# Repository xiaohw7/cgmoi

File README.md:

# CGMOI User Guide

## Overview

The CGMOI machine is one that is capable of measuring the Centre of Gravity (CG) and Moment Of Inertia (MOI) of a nano-satellite while satellite is mounted on the top plate as shown in picture below.

The concept of this machine is based on [this research paper](https://github.com/xiaohw7/cgmoi/blob/main/applsci-08-00104.pdf) done by researchers from ZheJiang University. It uses 3 load cells in a circle spaced 120 degrees apart to measure CG and a gyroscope to measure acceleration which in turn can be used to obtain MOI.

The machine also includes a stepper motor that spins the top plate, and linear actuators to raise and lower the load cells in order to measure CG.

The stepper motor, linear actuator, gyroscope, load cells and other components are controlled by and wired to an Arduino mega board. The Arduino could then be plugged into a laptop running the Arduino IDE where code could be uploaded to run the CGMOI machine.

Each load cell is marked load cell 1/2/3 on the load cell itself. Linear actuator 1/2/3 correspond to load cell 1/2/3. i.e. linear actuator 1 is directly below load cell 1.

## Components of the CGMOI Machine

- HX711 analog to digital converter

- Single pole double throw(SPDT) relay

- Double pole double throw(DPDT) relay

- Gyroscope

- Power supply (12v and 36v)

- Printed circuit Board

## How to use

1. User would have to download the following Arduino libraries:
      - [HX711_ADC](https://github.com/olkal/HX711_ADC) for the load cells
      - [hanyazou](https://github.com/hanyazou/BMI160-Arduino) for the BMI160 gyroscope
      - [AccelStepper](https://github.com/waspinator/AccelStepper) for stepper motor and stepper motor driver
      - [FreeRTOS](https://github.com/feilipu/Arduino_FreeRTOS_Library) for running Real Time Operating System on Arduino
      - [SimpleKalmanFilter](https://github.com/denyssene/SimpleKalmanFilter) for running values through a Kalman filter to reduce noisy readings

2. Upload cgmoi2.ino onto Arduino and open Serial monitor. Serial monitor to use 9600 baud. Stepper motor driver should be set to 1600 pulse/rev.

3. Code uses FreeRTOS. There will be 4 tasks, namely Rotate, Gyro, Motor, and Cg. Code will suspend Rotate, Gyro, and Motor task immediately in void setup() and Cg task will run at highest priority.

4. Code has 3 modes. Mode CG runs Cg task, reads values from load cells and output CG and mass values. Mode MOI runs Motor and Gyro tasks and outputs angular acceleration values. Mode ROTATE runs Rotate task and allows user to rotate top plate a desired number of steps in either direction.

5. After uploading code, Arduino will be running mode CG and user can see output values from load cells on Serial monitor. User can either continue with mode CG to measure CG of satellite, switch to mode MOI to measure MOI of satellite instead or switch to mode ROTATE to rotate top plate to the desired orientation.

6. Mode CG: User intends to measure CG of satellite

      * Linear actuators must be fully extended.

      * It is advisable to test each linear actuator by moving them up and down individually for 1 second before raising all three actuators completely. Refer to "Commands to send" table below for commands to move actuators individually.

      * Ensure ***screw securing removeable shaft (shown below) is removed*** before sending '9' in Serial monitor to raise linear actuators completely. Then, send '11' in serial monitor to tare load cells before mounting satellite.

      * 

      * Directions of x and y axis are indicated on the top plate and also illustrated in "Calculations" section below.

      * To ease measuring process of CG, x and y axis on top plate must align with axis indicated in "Calculations" section below. Arrow of y axis must point directly away from load cell 1. Location of origin is the center of the top plate.

      * One way to align x and y axis is to align the marked line on the edge of the top plate with the number 1 indicated on load cell 1(marked line should be on the edge of the top plate and positioned 90 degrees counter clockwise from the gyroscope when looking from above the gyroscope mounting point). User can do so with the help of mode 3. An illustration is shown below.

      * 

      * While running task Cg, mass and CG coordinates can be read straight off the output on the Serial monitor. Refer to "Calculations" section below for x and y axis. Coordinates are in mm.

      * User can send '14' to switch to mode MOI and measure MOI of satellite.

      * User can send '16' to switch to mode ROTATE and to rotate top plate.

7. Mode MOI: user intends on measuring MOI of satellite

      * Linear actuators must be fully retracted. Send '10' while in mode CG to fully retract linear actuators.

      * Ensure screw securing removeable shaft (shown above) is secured, send '14' to switch from mode CG to mode MOI.

      * Mode MOI uses 'stepper' instance of AccelStepper class to control stepper motor.

      * Gyro and Motor tasks will run simultaneously and angular acceleration values can be read from serial monitor. Motor will spin back and forth to allow gyro to measure acceleration values. Once measurement process is finished, average acceleration will be displayed on serial monitor along with "Finish recording" message. User has 15 seconds to mount/dismount satellite before recording process starts again.

      * User should record down angular acceleration values with and without satellite mounted. Refer to "Calculations" section for the equations to obtain MOI.

      * While running mode MOI, user can also send '15' to switch to mode CG and return to reading values from load cells.

      * While running mode MOI, user can send '16' to switch to mode ROTATE to rotate top plate.

8. Mode ROTATE: user intends to rotate top plate

      * Linear actuators must be fully retracted. Send '10' while in mode CG to fully retract linear actuators.

      * Ensure screw securing removeable shaft (shown above) is secured, send '16' to switch from mode CG to mode ROTATE.

      * User can input number of steps user wishes stepper motor to turn.

      * Mode ROTATE uses 'rotate' instance of the AccelStepper class. A separate instance from the one used in mode MOI. Hence when user first uploads `cgmoi2.ino`, mode ROTATE regards the position of the stepper motor at that instant as 0 (origin). User can instruct stepper motor to rotate to a specific position that is a certain number of steps away from the origin. Positive steps are in the clockwise direction from origin while negative steps are in the counter clockwise direction from origin.

      * Note that location of origin stays the same the whole time while using the code until Arduino is refreshed. Therefore if user inputs 3000 (motor rotates 3000 steps in clockwise direction from origin) and then inputs 1000, motor would subsequently rotate 2000 steps in the counter clockwise direction and stop at the position that is 1000 steps clockwise from the origin.

      * If user uses mode ROTATE to rotate to 3000 steps clockwise, and then proceeds to use mode MOI, mode MOI will alter the position of the stepper motor but mode ROTATE will still think it is at 3000 steps clockwise. Hence if user then goes back to mode ROTATE and inputs 0, motor will rotate 3000 steps counter clockwise.

      * ***Ensure serial monitor is set to 'No line ending'.***

      * While running mode ROTATE, user can send '15' to switch to mode CG and return to reading values from load cells.

      * While running mode ROTATE, user can send '14' to switch to mode MOI and measure MOI of satellite.

Below is an illustration of how to navigate between the three modes:

***
```
            (User uploads code)
                 |       
                 |   ----------------<--------------------------   
                 |   |                                         |
                 v   v                                         |
            -->(Mode CG)------->---------------                |
            |      |                          |                |
*send '15'* |      | *send '14'*              | *send '16'     ^ *send '15'*
            ^      |                          |                |
            |      v        *send '16'        v                |
            ---(Mode MOI)--------->----(Mode ROTATE)----->------
                   ^                          |
                   |       *send '14'         |
                   -------------<--------------  
```
***

## Commands to send

|Mode |Commands that can be sent |What it does|
|-----|--------------------------|------------|
|CG |Send '1' |Turn on power to linear actuators|
|CG |Send '2' |Turn off power to linear actuators|
|CG |Send '3'/'5'/'7' |Move linear actuator 1/2/3 up for 1 second|
|CG |Send '4'/'6'/'8' |Move linear actuator 1/2/3 down for 1 second|
|CG |Send '9' |Move all 3 linear actuators up fully|
|CG |Send '10' |Move all 3 linear actuators down fully|
|CG |Send '11' |Tare all load cells|
|CG |Send '12' |Turn on power to stepper motor|
|CG |Send '13' |Turn off power to stepper motor|
|CG |Send '14' |End Cg task and resume/start Gyro and Motor tasks, switch to mode MOI|
|CG |Send '16' |End Cg task and resume/start Rotate task, switch to mode ROTATE|
|MOI |Send '12' |Turn on power to stepper motor|
|MOI |Send '13' |Turn off power to stepper motor|
|MOI |Send '15' |End Gyro and Motor tasks and resume/start Cg task, switch to mode CG|
|MOI |Send '16' |End Gyro and Motor tasks and resume/start Rotate task, switch to mode ROTATE|
|ROTATE |Send '12' |Turn on power to stepper motor|
|ROTATE |Send '13' |Turn off power to stepper motor|
|ROTATE |Send '14' |End Rotate task and resume/start Gyro and Motor tasks, switch to mode MOI|
|ROTATE |Send '15' |End Rotate task and resume/start Cg task, switch to mode CG|
|ROTATE |Send steps to rotate |Motor rotate to set steps|

## Points to take note

- Before raising/lowering linear actuators, user must remember to ***remove screw securing removeable shaft***.

- When lowering top plate, user should stand by and make sure removeable shaft enters designated slot correctly.

- Before measuring CG, user to ensure that the tips of adjustable screws (shown below) on load cells are the same distance above the table top so that when top plate is resting on load cells, top plate is as flat as possible.

- Before measuring MOI, ensure screw securing removeable shaft is tightened to prevent any play when motor is turning.

- FreeRTOS can be buggy which causes starting position of gyroscope to shift after repeatedly using mode MOI. Hence it is recommended to position gyro chip above red tape using mode ROTATE before using mode MOI to measure angular acceleration.

- There is a tendency for SPDT relay supplying power to stepper motor to get stuck in the close position despite the LED light being off and signal sent to it to disconnect. This may be because relay is only rated for 30V while power supply is at 36V. Tapping the blue box on the relay would help to disconnect it. User can tell if power had been disconnected by observing light on stepper motor driver.

- Angular acceleration values is rather unreliable and difference while loaded and unloaded may not be easily observed. Sometimes loaded values may even be higher than unloaded values. May be due to looseness and play at the epoxy region of removeable shaft.

- First measurements of angular velocity tend to be buggy and inaccurate, hence code only starts recording values from second reading onwards.

- If load cell readings become inaccurate, try running "Calibration" example from this [github library](https://github.com/olkal/HX711_ADC) and obtain calibration values for each individual load cell and input into the code.

- If there is a need to stop measurements/linear actuators/stepper motor immediately, unplug Arduino to "Emergency Stop".

## Calculations

With reference to image above, points A,B,C correspond to load cell 1,2,3 respectively. Load cell numbers are marked on load cells.

1. Finding Mass

      * Pa = m4 - m1
      * Pc = m6 - m3
      * Pb = m5 - m2
      * Mass of satellite, M = Pa + Pb + Pc  
      * m1, m2 and m3 are weights of fixture tools and platform on load cell A, B and C respectively.
      * m4, m5 and m6 are weights of fixture tools, platform and satellite on load cell A, B and C respectively.
      * Pa, Pb and Pc are satellite weights on load cell a, b and c respectively.
      * Code outputs overall mass of satellite in grams.

2. Finding Centre of Gravity

      * Y-coordinate, yG = [Pb(y2) + Pc(y3) − Pa(y1)]/M
      * X-coordinate, xG = [Pb(x1) − Pc(x2)]/M
      * y1, y2, y3 are distances of points A, B, ad C from y-axis respectively. y1 = 206mm, y2 and y3 = 103mm
      * x1, x2, are distances of point B and C from x-axis. x1 and x2 = 178.4mm
      * Lengths are calculated using values from [load cell plate drawing](https://github.com/xiaohw7/cgmoi/blob/main/M02_load%20cell%20plate_drawing.pdf) and [load cell data sheet](https://github.com/xiaohw7/cgmoi/blob/main/M02_load%20cell%20plate_drawing.pdf).
      * To obtain z-coordinate of CG, rotate satellite by 90 degrees and undergo same calculations to obtain z-coordinate.
      * Code outputs coordinate of CG with reference to axis above and in millimeters.

3. Finding Moment Of Inertia

      * 

      * Use equation above to obtain J1. Where J1 is MOI of satellite. J0 is MOI of fixture tools which can be obtained from solid works. Shown in picture below, J0 in the vertical axis, taken at output coordinate system with center of top plate as origin, is ***19113908.45 grams * square millimeters***.
      * 
      *  Referring again to equation to obtain J1, w0 is angular velocity at time t without satellite. w’0 is angular velocity at time t with satellite. t1 and t2 are time at which angular velocity w0 and w’0 is taken respectively.
      * Thus it is observed that the fraction in the equation is angular acceleration without satellite mounted divided by angular acceleration with satellite mounted.
      * Code outputs angular acceleration values in degrees/sec^2 which can then be used to calculate J0.

      * Rotating about X-axis of satellite will result in JX

      * Rotating about Y-axis of satellite will result in JY

      * Rotating about Z-axis of satellite will result in JZ

      * 

      * Above equation uses parallel axis parallel axis theorem to correct MOI vector with reference to the CG and find vector of MOI. JxG, JyG, JzG are the MOI in x, y, and z direction respectively.

## Areas for improvement

1. Values for angular acceleration can vary substantially leading to inaccurate and imprecise values of MOI.

     * One way to improve is to move designated mounting place of BMI160 chip to the center of the top plate. This way Arduino can use raw values of angular velocity measured by the gyroscope in the MOI equation instead of having to measure linear acceleration values and then subject them to a series of calculations to obtain angular acceleration.

     * Another way is to decrease the play in the removeable shaft especially at the spot with Epoxy where the shaft connects with the flat plate.

2. Torque of stepper motor varies with speed and is difficult to control. This may lead to inaccurate values of MOI when torque applied while top plate is loaded vs when it is unloaded is different.

     *  Potential way to improve is to change to motor to a simple DC motor that outputs constant torque every time it accelerated top plate from rest regardless of whether top plate is loaded.

3. PCB enclosure was not fully printed because filament kept breaking during the print. 2 halves of the enclosure were used as a makeshift PCB enclosure with one end of sawn open to create opening for wires. Also, slot for PCB to sit in and the width of the enclosure was too narrow for PCB to fit and required a lot of filing. Even then PCB had difficulty fitting into the slot.

      * To increase probability of success of subsequent prints, opening of PCB enclosure should be widened by 1-2mm. Height of slot meant for PCB should be increased by 1mm. Walls of enclosure can also be made thinner for a faster print. And use filament that's less likely to break during print.

## Instructions
Below are instructions on how to set up each individual component of the CGMOI machine, links to each component's datasheet, as well as some notes I made on the my experiences.

### HX711 ADC and load cells:

- Refer to [this link](https://makersportal.com/blog/2019/5/12/arduino-weighing-scale-with-load-cell-and-hx711) for instructions on how to connect load cell to HX711 to Arduino. All 3 load cells can share a common power and ground connection.

- Download library at [github](https://github.com/olkal/HX711_ADC) for examples on calibrating and reading values from multiple load cells.

- To calibrate load cell, connect Arduino to an individual load cell through HX711 and run “Calibration” example. Follow instructions on the serial monitor and record down “calibration value”.  Do this for every individual load cell.

- Use `HX711_script3.ino` to read all 3 load cells. Input “calibration values” of each respective load cell into the code. Weight reading is taken 10 times with 0.05sec intervals and average weight on each load cell is obtained. Calculations are then made with the average weights. Run the code and read values of weight and coordinates of CG from serial monitor.

- Send “t” on serial monitor to tare load cells immediately.

- Reading is in grams. CG units are in mm.

- [HX711 data sheet](https://onedrive.live.com/?authkey=%21AlhODXygXZWnhUQ&cid=0008E16A592663A6&id=8E16A592663A6%2129427&parId=8E16A592663A6%2129388&o=OneUp)

- [Load cell data sheet](https://onedrive.live.com/?authkey=%21AlhODXygXZWnhUQ&cid=0008E16A592663A6&id=8E16A592663A6%2129434&parId=8E16A592663A6%2129388&o=OneUp)

### BMI 160 Gyro:

- Refer to [hanyazou's github](https://github.com/hanyazou/BMI160-Arduino) for instructions to connect to gyro sensor. Download library at the same website. Use example `Gyro` example or `bmi_160_gyro_script.ino` to read from sensor. Switch example code to I2C mode.

- Another library that can read from gyro is [DFRobot](https://github.com/DFRobot/DFRobot_BMI160#installation). Download the library and use `accelgyro` example for both accelerometer and gyroscope readings.

- `bmi_160_gryo_script2.ino` takes `accelgyro` example from DFRobot library and modifies it to obtain net acceleration from x and y axis using Pythagoras theorem. Measurements are taken every 0.1 seconds and the average of 10 readings are calculated. Acceleration is converted from g to degrees/sec^2.

- `bmi_160_gryo_script3.ino` modifies `bmi_160_gyro_script.ino` to get net acceleration using Pythagoras theorem on the x an y axis acceleration values.

- Net acceleration is then divided by radius (distance from gyro to center of top plate) to obtain angular acceleration in radians which is then converted to degrees.

- Sensor is to use 3.3v from Arduino.

- Helpful links at [arduino projects](http://www.arduinoprojects.net/sensor-projects/using-bmi160-sensor-arduino-uno.php) and [sparkfun.](https://learn.sparkfun.com/tutorials/gyroscope/all)

- [BMI 160 datasheet](https://onedrive.live.com/?authkey=%21AlhODXygXZWnhUQ&cid=0008E16A592663A6&id=8E16A592663A6%2129414&parId=8E16A592663A6%2129388&o=OneUp)

### Linear actuator with relay:

- One SPDT relay to be used as overall power switch to linear actuators. 3 DPDT relays to be used as switches for each individual actuator and to be connected in a way to allow current to flow in both direction so as to enable actuator to extend and retract.

- Helpful links for SPDT relay can be found at [circuit basics](https://www.circuitbasics.com/setting-up-a-5v-relay-on-the-arduino/) and [last minute engineers](https://lastminuteengineers.com/one-channel-relay-module-arduino-tutorial/).

- Wiring for DPDT relay to be able to reverse current polarity to actuators can be found at [digikey](https://forum.digikey.com/t/polarity-reversal-using-a-dpdt-switch/626/4).

- Wiring:

- Above picture shows wiring of linear actuators with relays.

- VCC and GND of all relays are connected to 5V and GND of Arduino through breadboard.

- For each DPDT relay, NO2 and NC1 should be connected to the black wire of actuator while NO1 and NC2 should be connected to the red wire of actuator.

- Use `linear_actuator_script.ino` to control the actuators by sending commands through serial monitor.

|Commands that can be sent |What it does|
|--------------------------|------------|
|Send '1'|Power on|
|Send '2'|Power off|
|Send '3'/'5'/'7'|Move actuator 1/2/3 up for 1 sec|
|Send '4'/'6'/'8'|Move actuator 1,2,3 down for 1 sec|
|Send '9'|Move all 3 actuators up completely|
|Send '10'|Move all 3 actuators down completely|

- Linear actuator to use 12V from power supply.

- [Linear actuator data sheet](https://onedrive.live.com/?authkey=%21AlhODXygXZWnhUQ&cid=0008E16A592663A6&id=8E16A592663A6%2129428&parId=8E16A592663A6%2129388&o=OneUp)

- [spdt relay datasheet](https://onedrive.live.com/?authkey=%21AlhODXygXZWnhUQ&cid=0008E16A592663A6&id=8E16A592663A6%2129439&parId=8E16A592663A6%2129388&o=OneUp)

- [dpdt relay datasheet](https://datasheetspdf.com/datasheet/HK19F-DC5V.html)

### LICHUAN LCDA257S stepper motor driver and stepper motor:

- See [dronebotworkship](https://dronebotworkshop.com/big-stepper-motors/) to get an overview on stepper drivers and motors.

- See [makersguides](https://www.makerguides.com/tb6600-stepper-motor-driver-arduino-tutorial/) for example code and wiring.

- Number of pulses per round can be adjusted by referring to table on the driver.

- Download AccelStepper library from [github](https://github.com/waspinator/AccelStepper).

- In AccelStepper library, speed is in steps/sec, Acceleration is in steps/sec2, position is in number of steps.

- `Stepper_motor_driver.ino` controls stepper motor directly while `Stepper_motor_driver2.ino` uses AccelStepper library to control motor.

- Another way of accelerating stepper motor is do gradually quicken pulses sent to motor (ramping). Code is in `Stepper_motor_driver3.ino`.

- Another sketch based on is conjured up Stepper_motor_driver2.ino is conjured up with the intention of enabling user to input number of steps the user wishes the stepper motor to rotate. Code is in `rotate_topplate.ino`. Starting position of stepper motor when user first uploads the code is always regarded as the origin. User can instruct stepper motor to rotate to a specific position that is a certain number of steps away from the origin. Positive steps are in the clockwise direction from the origin while negative steps are in the counter clockwise direction from the origin. Note that location of origin stays the same the whole time while using the code and only changes if user resets the Arduino or uploads the code again.

- There was a problem of code running twice for one input. Problem was solved by setting serial monitor to 'No line ending'. Code is in `rotate_topplate.ino`.

- Stepper motor to use 36V from power supply.

- [Stepper motor driver datasheet](https://onedrive.live.com/?authkey=%21AlhODXygXZWnhUQ&cid=0008E16A592663A6&id=8E16A592663A6%2129431&parId=8E16A592663A6%2129388&o=OneUp)

- [Stepper motor datasheet](https://onedrive.live.com/?authkey=%21AlhODXygXZWnhUQ&cid=0008E16A592663A6&id=8E16A592663A6%2129413&parId=8E16A592663A6%2129388&o=OneUp)

### Putting it together (Gyro and Motor):

- Function to control movement of stepper motor in AccelStepper library is blocking, thus we use FreeRTOS on Arduino, Gyro and Motor can run and read data simultaneously. FreeRtos library can be found at [github](https://github.com/feilipu/Arduino_FreeRTOS_Library).

- `moi.ino`(`Stepper_motor_driver2.ino` + `bmi_160_gryo_script3.ino`) uses FreeRTOS and AccelStepper library to run motor and gyro simultaneously.

- Alternatively, we can use Pulse Width Modulation to send pulses to stepper motor. analogWrite() function output a PWM signal to stepper motor and is not a blocking function. Hence can collect data from gyro immediately after starting stepper motor.

- Code to toggle PWM frequencies in Arduino can be found  [here](https://www.etechnophiles.com/how-to-change-pwm-frequency-of-arduino-mega/).

- Take note: code to change PWM frequency to 62500 Hz changes delay() function such that delay(1000000) now is approximately 15 sec.

- Also, offset values are recorded so as to account for gyro not being completely flat. Code can be found in `moi2.ino` (using PWM to control stepper motors + `bmi_160_gryo_script2.ino`).

- However, Gyro still experiences large amount of noise. To reduce noise, gyro code include a digital low pass filter in the code from [hanyazou's github](https://github.com/hanyazou/BMI160-Arduino).  Also, a simple Kalman Filter found on [github] (https://github.com/denyssene/SimpleKalmanFilter) is added into the code which decreased standard variation when top plate is stationary as well as when it is moving, the final angular acceleration value is put through the filter.  

- Using FreeRTOS and PWM with altered frequency of 31372.55 Hz, a graph of angular acceleration against time is plotted through the acceleration and deceleration of the stepper motor.  It is observed that there is a very sharp peak acceleration when stepper motor accelerates and acceleration. Hence the gyro will measure acceleration values throughout the motor’s acceleration and the code will record down the peak acceleration value.

- Gyroscope sample rate is changed from 200Hz to 1600Hz so as to increase accuracy. Peak acceleration values are put in an array and after a certain number or recordings, mean and standard deviation are calculated from the peak values in array. Code is in `moi3.ino` (using PWM to control stepper motors + `bmi_160_gryo_script3.ino`).

- However, peak acceleration values tend to vary substantially (sometimes up to 60%). We can use FreeRTOS to run gyro and motor with AccelStepper library simultaneously. Motor will accelerate at a set acceleration and gyro can measure average acceleration during that time.

- 3 tasks are created, namely Control, Motor and Gyro. Control task will run with highest priority and will first suspend Gyro and Motor task. Purpose of Control task is to take commands from serial monitor and start Gyro and Motor task to begin recording of values.

- While motor task is causing motor to accelerate, Gyroscope task will run and read acceleration values with each loop. Average acceleration is obtained by dividing total acceleration by number of loops variable loopCount. Average acceleration values are added to an array and a subsequent average is obtained at the end of a set number of recordings.

- When switching from Control task to Gyro and Motor task, first reading is buggy and inaccurate and hence not added to the array. Only 2nd reading onwards are added to the array. loopCount can also be used to limit gyro’s recording to the acceleration process of the motor and not both acceleration and deceleration.

- A new problem arise when load is put on top plate, average acceleration is observed to increase instead of decrease due to majority of acceleration values becoming higher despite peak acceleration becoming lower. This may be due to the usage of AccelStepper library which allows motor to draw more current to maintain set acceleration. Solution is to max out setAcceleration() and setMaxSpeed() functions so that motor could not draw any additional current and to set dip switches on the side of the stepper motor driver to 1600 pulses/round. Code is in `moi4.ino` (modified from `moi.ino`).

### Putting it together (Linear Actuator and Load Cells):
- Refer to above instructions “Linear actuator with relay” for instructions on how to operate linear actuators. Once Arduino is on, load cells are already reading weight values and calculating CG.

- Linear actuators should be tested first by moving each actuator up and down.

- Marked line at the edge of top plate should be aligned with number 1 indicated on loadcell 1 so that the axis indicated on the top plate correspond to calculations using the 3 load cells. Marked line should be 90 degrees counter clockwise from gyroscope when looking from the top view.

- Linear actuators should be extended all the way to measure weight of satellite. Satellite should be placed on the top plate after actuators fully extend and taring load cells. Wait for “Tare load cell 1 / 2 / 3 complete” message. User should also tare load cells after each measurement.

- Arduino mega is able to support all 3 load cells and the 4 relays hence all 7 components will share the same VCC and GND through breadboard. Code is in `cg.ino` (`linear_actuator_script.ino` + `HX711_script3.ino`).

### Putting it together (CG and MOI):

- Code uses FreeRTOS. There will be 3 tasks, namely Gyro, Motor and Cg. Code will suspend Gyro and Motor task in void setup(). Cg will run at highest priority.

- While running task Cg, user can control linear actuators and read values from load cells. User can send command to suspend Cg task and resume Gyro and Motor task in order to start obtaining angular acceleration values. While running Gyro and Motor task, user can also send command to suspend Gyro and Motor task and resume Cg task to return to reading values from linear actuators. Code is in `cgmoi.ino`(`moi4.ino` + `cg.ino`).

- To facilitate more accurate and easier measurements of CG, another task, based on `rotate_topplate.ino`, is added to the code. Rotate task uses a separate instance of AccelStepper class from the one used in Motor task and allows user to control stepper motor and rotate top plate a set number of steps in either direction to facilitate alignment of top plate before raising linear actuators to measure CG. New code has 4 tasks, namely Gyro, Motor, Cg, and Rotate. Code is in `cgmoi2.ino`.

### Putting it together (Printed Circuit Board):

- The Arduino Mega board along with relays and ADCs are to be stacked on top of the PCB.

- Wiring of components of CGMOI machine such as load cells, gyro, ADC to Arduino on PCB will be done with screw terminals soldered onto PCB.

- Female headers will be soldered on to PCB so that relays and ADCs can be stacked on PCB.

- Male headers will be soldered on to PCB so that Arduino Mega can be stack on the PCB.

- PCB along with its components would be put into a PCB encloser with opening for wires to connect to other components.

- PCB was designed using KiCad and the files can be found [here](https://github.com/xiaohw7/cgmoi/tree/main/pcb/CGMOI).

- PCB encloser is designed using solidworks and to be 3D printed. Design of encloser is based on [this PCB encloser](https://www.lazada.sg/products/extruded-pcb-aluminum-box-black-enclosure-electronic-project-case-80x160x170mm-i2083438345-s11541324037.html)

- PCB CAD files can be found on [Onedrive](https://onedrive.live.com/?authkey=%21AlhODXygXZWnhUQ&id=8E16A592663A6%2154244&cid=0008E16A592663A6)

- [Screw terminal to be used](https://www.digikey.sg/en/products/detail/w%C3%BCrth-elektronik/691211720002/2060530 )

- [Female headers to be used](https://www.digikey.sg/en/products/detail/samtec-inc/SSW-101-01-G-D/6691946 )

- [Male headers to be used](https://www.digikey.sg/en/products/detail/sullins-connector-solutions/PREC003SAAN-RC/2774851?s=N4IgTCBcDaIMoEYAMCwFEDCBaJBmLAcgCIgC6AvkA)

- There was an error in the PCB design regarding dpdt 2 and dpdt 3. The input, vcc, com1, and com2 pins meant for dpdt2 has been wrongly placed at dpdt3 and vice versa. Fortunately, all dpdt relays share the same vcc, com1, and com2 so technically there is no impact there. As for the input pins, simply changing the Arduino code such that input pin of dpdt 2 is now the input pin of dpdt 3 and vice versa has solved the problem.

- 12v power supply for linear actuators do not function properly when connected to PCB. When linear actuators are turned on, 12v power supply stutters and its LED light flicker on and off. As a result, linear actuators also stutter. Actuators are able to function normally when benchtop power supply is connected to PCB. Actuators are also able to function normally when 12v power supply is connected to breadboard. This occurrence seems to be due to the start-up current required by 3 linear actuators being too high for the 12v power supply when connected to PCB. The solution is to lower the output of the 12v power supply to roughly 10.5v. This decreased the start-up current that 3 linear actuators require to a manageable amount for the 12v power supply allowing it to continue supplying power to move the actuators.

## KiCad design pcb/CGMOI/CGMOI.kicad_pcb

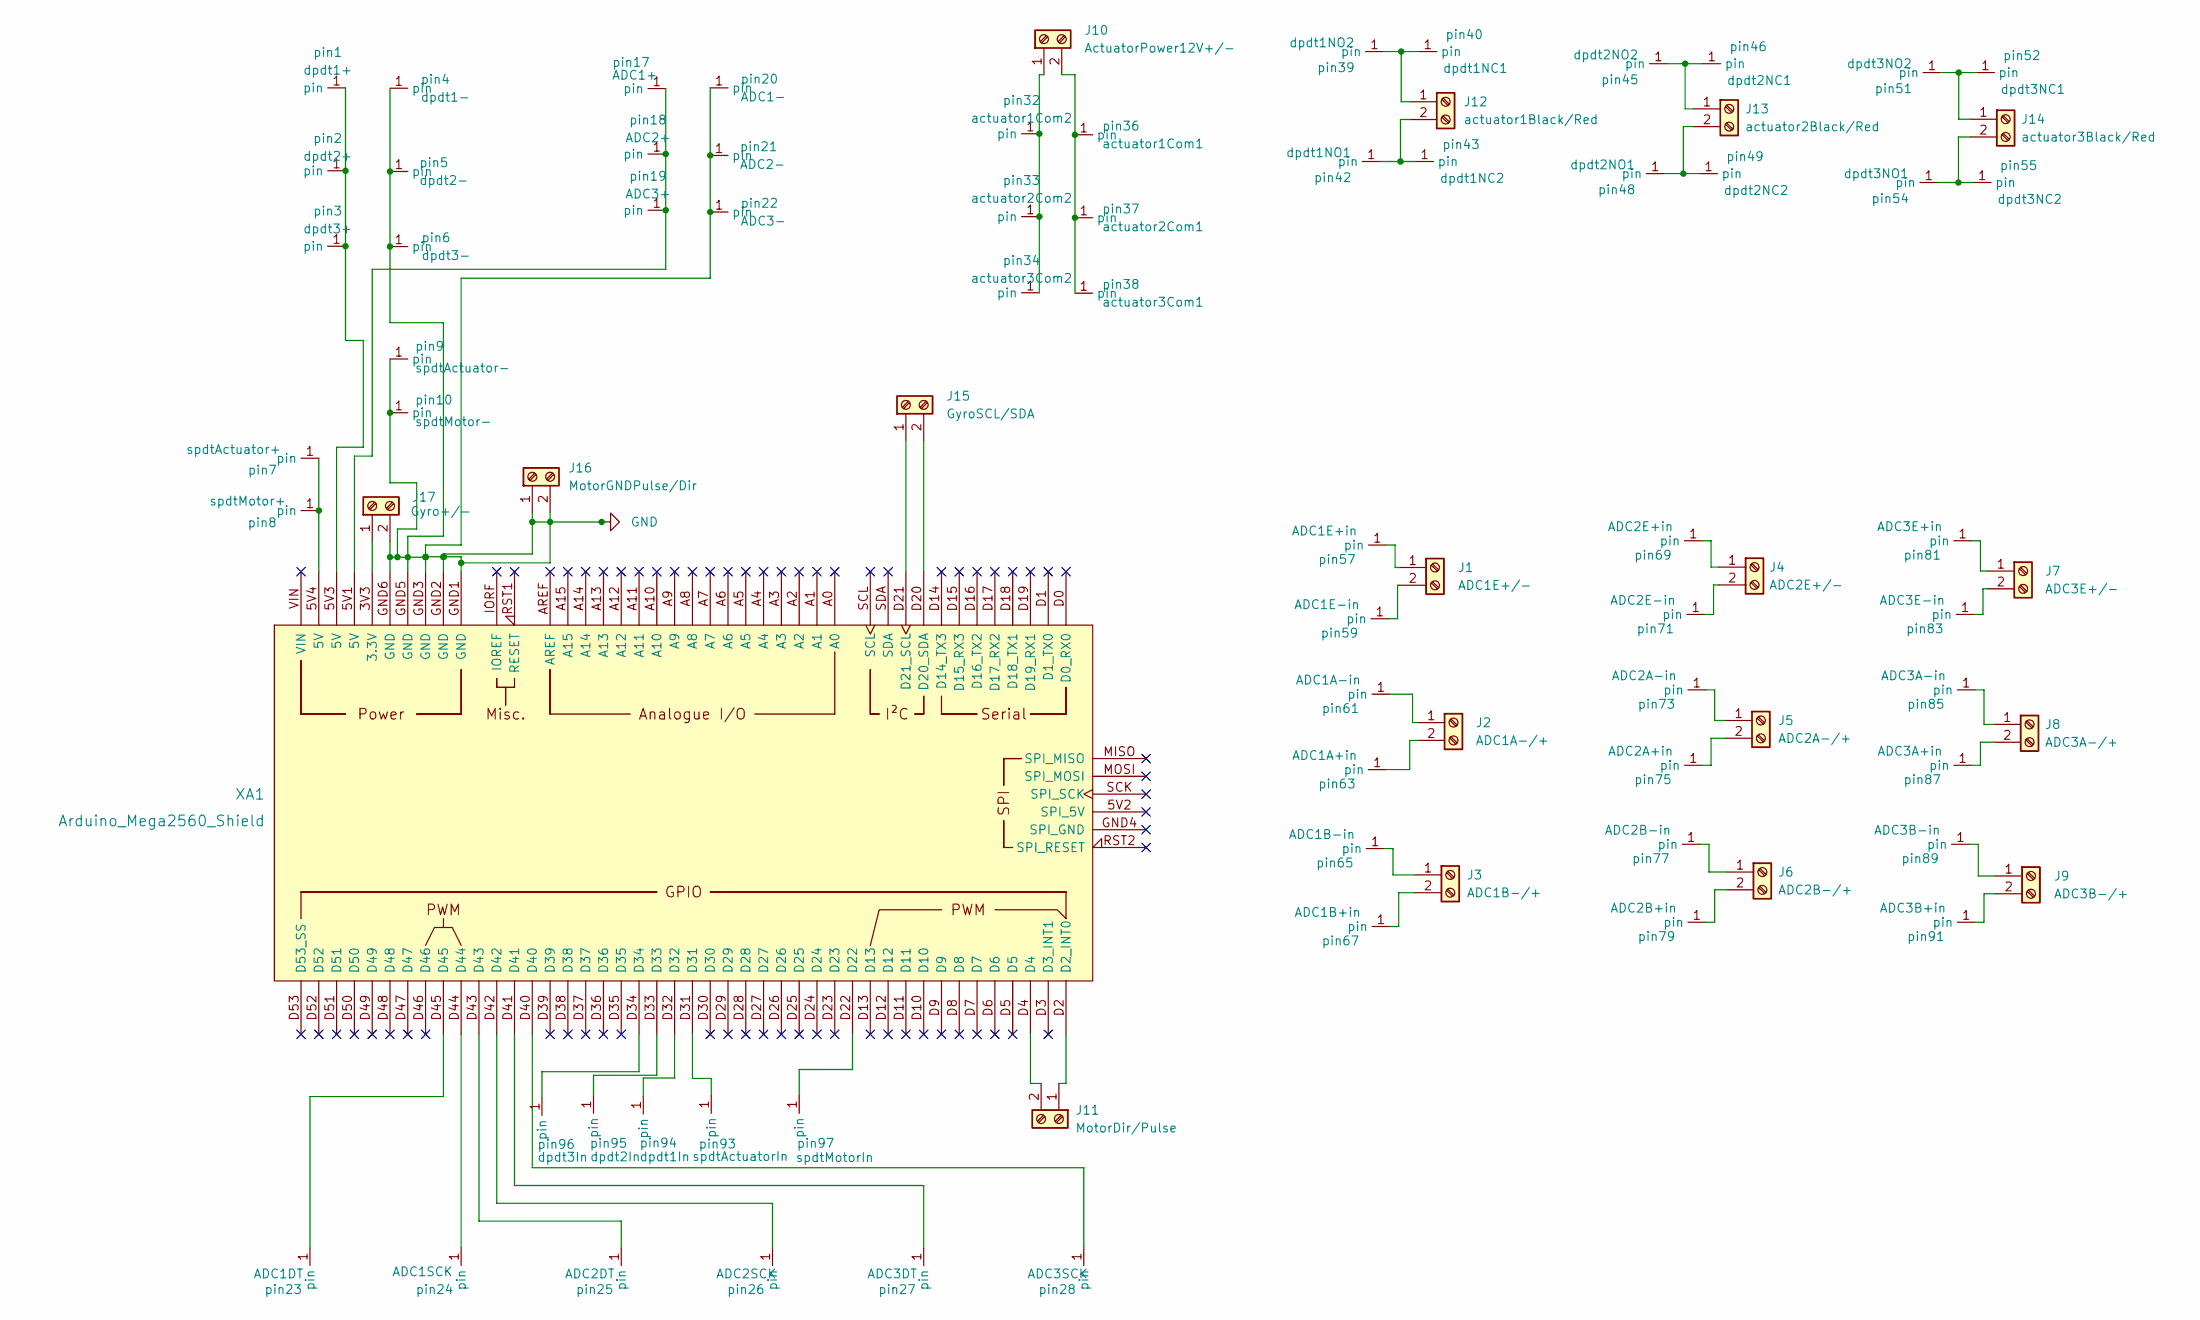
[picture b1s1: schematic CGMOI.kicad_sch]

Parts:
J1: ADC1E+/-; screw terminal
J2: ADC1A-/+; screw terminal
J3: ADC1B-/+; screw terminal
J4: ADC2E+/-; screw terminal
J5: ADC2A-/+; screw terminal
J6: ADC2B-/+; screw terminal
J7: ADC3E+/-; screw terminal
J8: ADC3A-/+; screw terminal
J9: ADC3B-/+; screw terminal
J10: ActuatorPower12V+/-; screw terminal
J11: MotorDir/Pulse; screw terminal
J12: actuator1Black/Red; screw terminal
J13: actuator2Black/Red; screw terminal
J14: actuator3Black/Red; screw terminal
J15: GyroSCL/SDA; screw terminal
J16: MotorGNDPulse/Dir; screw terminal
J17: Gyro+/-; screw terminal
XA1: Arduino_Mega2560_Shield
pin1: dpdt1+; pin
pin2: dpdt2+; pin
pin3: dpdt3+; pin
pin4: dpdt1-; pin
pin5: dpdt2-; pin
pin6: dpdt3-; pin
pin7: spdtActuator+; pin
pin8: spdtMotor+; pin
pin9: spdtActuator-; pin
pin10: spdtMotor-; pin
pin17: ADC1+; pin
pin18: ADC2+; pin
pin19: ADC3+; pin
pin20: ADC1-; pin
pin21: ADC2-; pin
pin22: ADC3-; pin
pin23: ADC1DT; pin
pin24: ADC1SCK; pin
pin25: ADC2DT; pin
pin26: ADC2SCK; pin
pin27: ADC3DT; pin
pin28: ADC3SCK; pin
pin32: actuator1Com2; pin
pin33: actuator2Com2; pin
pin34: actuator3Com2; pin
pin36: actuator1Com1; pin
pin37: actuator2Com1; pin
pin38: actuator3Com1; pin
pin39: dpdt1NO2; pin
pin40: dpdt1NC1; pin
pin42: dpdt1NO1; pin
pin43: dpdt1NC2; pin
pin45: dpdt2NO2; pin
pin46: dpdt2NC1; pin
pin48: dpdt2NO1; pin
pin49: dpdt2NC2; pin
pin51: dpdt3NO2; pin
pin52: dpdt3NC1; pin
pin54: dpdt3NO1; pin
pin55: dpdt3NC2; pin
pin57: ADC1E+in; pin
pin59: ADC1E-in; pin
pin61: ADC1A-in; pin
pin63: ADC1A+in; pin
pin65: ADC1B-in; pin
pin67: ADC1B+in; pin
pin69: ADC2E+in; pin
pin71: ADC2E-in; pin
pin73: ADC2A-in; pin
pin75: ADC2A+in; pin
pin77: ADC2B-in; pin
pin79: ADC2B+in; pin
pin81: ADC3E+in; pin
pin83: ADC3E-in; pin
pin85: ADC3A-in; pin
pin87: ADC3A+in; pin
pin89: ADC3B-in; pin
pin91: ADC3B+in; pin
pin93: spdtActuatorIn; pin
pin94: dpdt1In; pin
pin95: dpdt2In; pin
pin96: dpdt3In; pin
pin97: spdtMotorIn; pin

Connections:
GND: J16.1, J16.2, J17.2, XA1.GND1 (GND), XA1.GND2 (GND), XA1.GND3 (GND), XA1.GND5 (GND), XA1.GND6 (GND), pin4.1 (pin), pin5.1 (pin), pin6.1 (pin), pin9.1 (pin), pin10.1 (pin), pin20.1 (pin), pin21.1 (pin), pin22.1 (pin)
unnamed: J1.1, pin57.1 (pin)
unnamed: J1.2, pin59.1 (pin)
unnamed: J2.1, pin61.1 (pin)
unnamed: J2.2, pin63.1 (pin)
unnamed: J3.1, pin65.1 (pin)
unnamed: J3.2, pin67.1 (pin)
unnamed: J4.1, pin69.1 (pin)
unnamed: J4.2, pin71.1 (pin)
unnamed: J5.1, pin73.1 (pin)
unnamed: J5.2, pin75.1 (pin)
unnamed: J6.1, pin77.1 (pin)
unnamed: J6.2, pin79.1 (pin)
unnamed: J7.1, pin81.1 (pin)
unnamed: J7.2, pin83.1 (pin)
unnamed: J8.1, pin85.1 (pin)
unnamed: J8.2, pin87.1 (pin)
unnamed: J9.1, pin89.1 (pin)
unnamed: J9.2, pin91.1 (pin)
unnamed: J10.1, pin32.1 (pin), pin33.1 (pin), pin34.1 (pin)
unnamed: J10.2, pin36.1 (pin), pin37.1 (pin), pin38.1 (pin)
unnamed: J11.1, XA1.D2 (D2_INT0)
unnamed: J11.2, XA1.D4
unnamed: J12.1, pin39.1 (pin), pin40.1 (pin)
unnamed: J12.2, pin42.1 (pin), pin43.1 (pin)
unnamed: J13.1, pin45.1 (pin), pin46.1 (pin)
unnamed: J13.2, pin48.1 (pin), pin49.1 (pin)
unnamed: J14.1, pin51.1 (pin), pin52.1 (pin)
unnamed: J14.2, pin54.1 (pin), pin55.1 (pin)
unnamed: J15.1, XA1.D21 (D21_SCL)
unnamed: J15.2, XA1.D20 (D20_SDA)
unnamed: J17.1, XA1.3V3 (3.3V)
unnamed: XA1.5V1 (5V), pin17.1 (pin), pin18.1 (pin), pin19.1 (pin)
unnamed: XA1.5V3 (5V), pin1.1 (pin), pin2.1 (pin), pin3.1 (pin)
unnamed: XA1.5V4 (5V), pin7.1 (pin), pin8.1 (pin)
unnamed: XA1.D22, pin97.1 (pin)
unnamed: XA1.D31, pin93.1 (pin)
unnamed: XA1.D32, pin94.1 (pin)
unnamed: XA1.D33, pin95.1 (pin)
unnamed: XA1.D34, pin96.1 (pin)
unnamed: XA1.D40, pin28.1 (pin)
unnamed: XA1.D41, pin27.1 (pin)
unnamed: XA1.D42, pin26.1 (pin)
unnamed: XA1.D43, pin25.1 (pin)
unnamed: XA1.D44, pin24.1 (pin)
unnamed: XA1.D45, pin23.1 (pin)

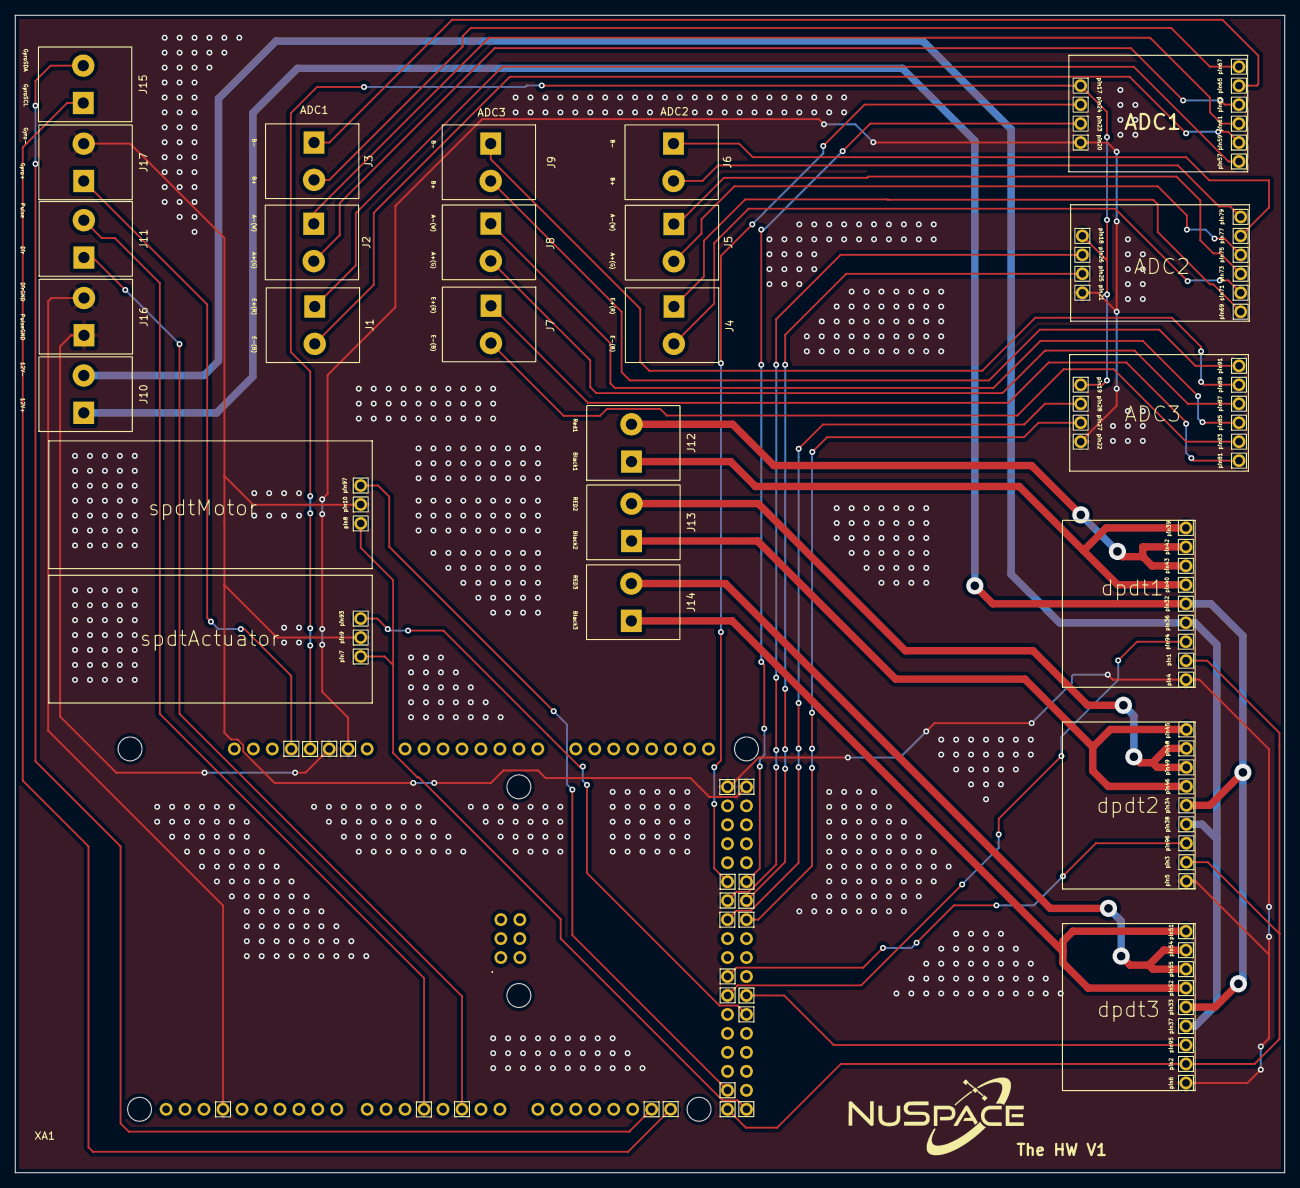
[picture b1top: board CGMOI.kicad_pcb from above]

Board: 2 copper layers, 170.0 x 155.0 mm, 81 parts (1 on the bottom side), 46 nets.

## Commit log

2022-04-07 Create Arduino Codes
2022-04-07 Create cg
2022-04-07 Create k
2022-04-07 Create Calculations
2022-04-07 test
2022-04-11 set date
2022-04-13 1304
2022-04-13 readme
2022-04-14 stepper motor commands
2022-04-20 2004 with new moi4 using freertos
2022-04-20 2004 second
2022-04-26 2604
2022-04-26 coordinates pic
2022-04-26 pic in readme
2022-04-26 redme
2022-04-26 parallel
2022-04-26 readme loadcell
2022-04-26 loadcell
2022-04-27 read me linear actuator
2022-04-27 readme stepper motor
2022-04-27 readme edits
2022-04-28 add table in readme
2022-04-28 table for readme
2022-04-28 line in readme table
2022-04-28 mainly readme eddits
2022-04-29 readme pointers
2022-04-29 literary review
2022-04-29 literary review link in readme
2022-04-29 readme indentation
2022-04-29 indentation
2022-04-29 cgmoi machine pic
2022-04-29 readme cgmoi pic
2022-04-29 2904
2022-05-04 screw securing shaft pic
2022-05-04 readme screw securing removeable shaft pic
2022-05-12 1205
2022-05-12 satellite mounted picture
2022-05-12 readme mounted satellite pic
2022-05-18 readme pcb section
2022-05-19 pcb1905
2022-05-23 new screw terminal link in readme
2022-05-24 pcb 2405
2022-05-24 moi of topplate picture
2022-05-24 top plate moi pic
2022-05-24 readme top plate moi pic
2022-05-24 moi top plate pic with arrow
2022-05-25 final pcb with gerbe file
2022-05-26 readme pcb components
2022-05-26 readme flow chart
2022-05-27 readme points for improvement
2022-05-27 editted coordinates
2022-05-27 readme edited coordinates
2022-05-27 edited coordinate
2022-05-27 readme edited coordinates pic
2022-05-27 load cell and load cell plate drawing
2022-05-27 annotated pictures
2022-05-27 readme annotated pic
2022-05-27 gyro pic
2022-05-30 load cell screw pic and readme cgmoi component pics
2022-06-03 read me pcb updates
2022-06-03 axis alignment pic
2022-06-03 axis alignment pic readme
2022-06-08 readme stuttering actuators solved
2022-06-08 pcb cad link
2022-06-08 power supply pic
2022-06-08 readme power supply pic
2022-06-08 pcb pic
2022-06-08 readme pcb pic
2022-06-08 0806
2022-06-09 readme update on Rotate task
2022-06-09 arduino codes 0906
2022-06-10 1006
2022-06-14 readme mode update
2022-06-14 arduino codes 1406
2022-06-15 slides
2022-06-16 slides update
